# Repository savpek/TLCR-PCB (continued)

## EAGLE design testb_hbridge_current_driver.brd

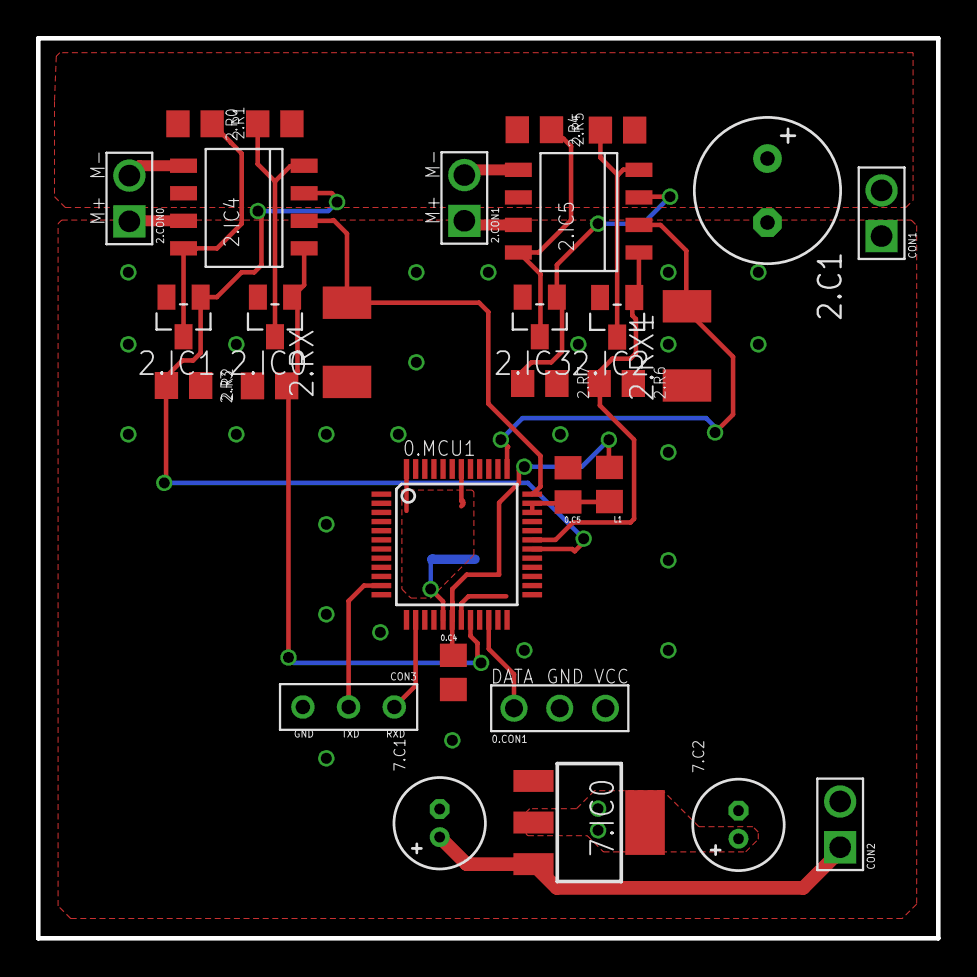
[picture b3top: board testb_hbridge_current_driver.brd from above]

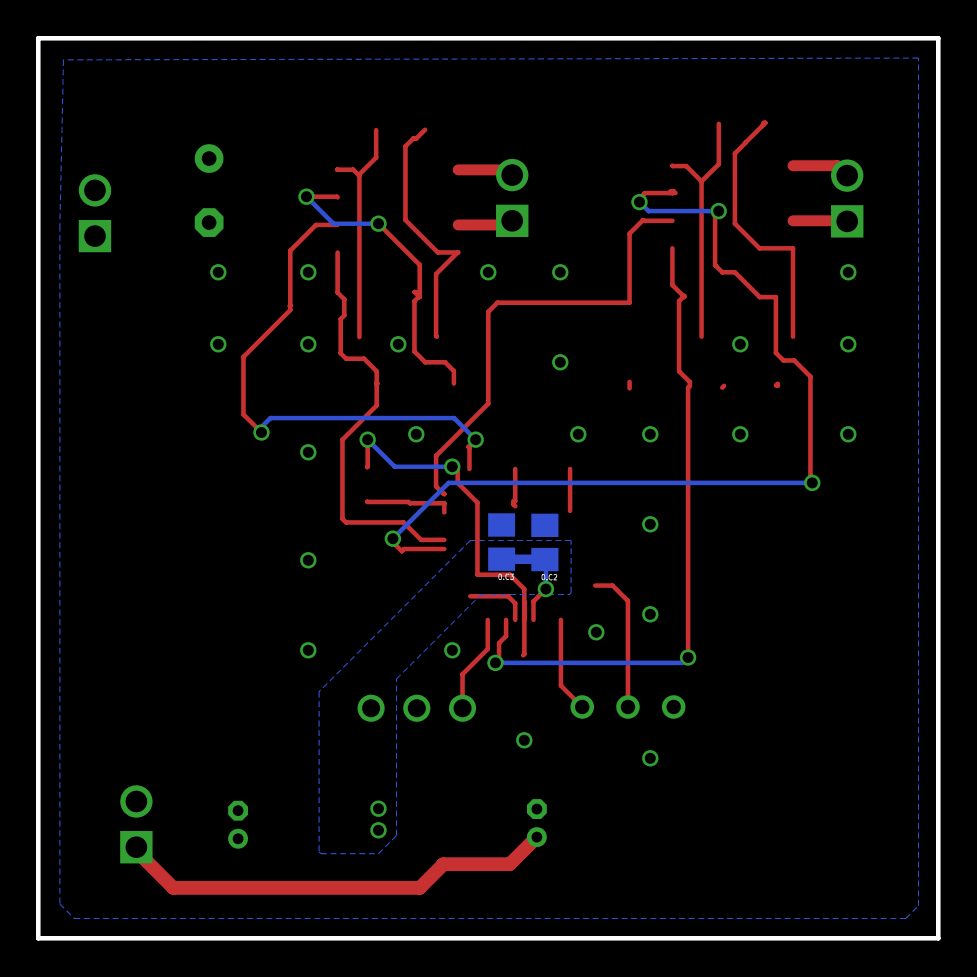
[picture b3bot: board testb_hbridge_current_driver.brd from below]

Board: 2 copper layers, 50.0 x 50.0 mm, 32 parts (2 on the bottom side), 23 nets.

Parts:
0.C2, 0.C3, 0.C4, 0.C5: 100nF; C0805
0.CON1: CONNECTOR_3PINAWIRE; 1X3_AWIRE
0.MCU1: AT32UCL016/32/64_TQFP48; TQFP48
2.C1: 220uF; E3,5-8
2.CON0, 2.CON1: CONNECTOR_2PIN1X2_MOTOR_COIL; 1X2_MOTOR_COIL_CONNECTOR
2.IC0, 2.IC1, 2.IC2, 2.IC3: N_MOSFET_TSM2N7002; SOT23
2.IC4, 2.IC5: ZXMHC6A07T8
2.R0, 2.R1, 2.R4, 2.R5: 1k; R0805
2.R2, 2.R3, 2.R6, 2.R7: 10k; R0805
2.RX, 2.RX1: 0R2; R2010
7.C1, 7.C2: 22uF; E1.5-5
7.IC0: REGULATOR_AP1117E33G-13; SOT223
CON1, CON2: CONNECTOR_2PIN1X2_WIRE; 1X2_WIRE
CON3: CONNECTOR_3PINUSART; 1X3_USART
L1: 10uH; C0805

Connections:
#RESET(AWIRE_DATA): 0.CON1.DATA, 0.MCU1.22
+3V3: 0.C2.1, 0.C3.1, 0.CON1.VCC, 0.MCU1.17, 0.MCU1.42, 0.MCU1.48, 7.C2.+, 7.IC0.2, 7.IC0.4
+12V: 2.C1.+, 2.IC4.6, 2.IC5.6, 2.R0.2, 2.R1.2, 2.R4.2, 2.R5.2, CON1.2
GND: 0.C2.2, 0.C3.2, 0.C4.2, 0.C5.2, 0.CON1.GND, 0.MCU1.1, 0.MCU1.19, 0.MCU1.33, 0.MCU1.43, 0.MCU1.45, 2.C1.-, 2.IC0.2, 2.IC1.2, 2.IC2.2, 2.IC3.2, 2.R2.1, 2.R3.1, 2.R6.1, 2.R7.1, 2.RX.1, 2.RX1.1, 7.C1.-, 7.C2.-, 7.IC0.1, CON1.1, CON2.2, CON3.GND
unnamed: 7.C1.+, 7.IC0.3, CON2.1
unnamed: 2.IC0.3, 2.IC4.4, 2.R0.1
unnamed: 2.CON0.M+, 2.IC4.7
unnamed: 2.CON0.M-, 2.IC4.5
unnamed: 0.C5.1, 0.MCU1.34, 0.MCU1.35, L1.1
unnamed: 0.C4.1, 0.MCU1.18, L1.2
unnamed: 2.IC2.3, 2.IC5.4, 2.R4.1
unnamed: 2.IC1.3, 2.IC4.8, 2.R1.1
unnamed: 2.IC3.3, 2.IC5.8, 2.R5.1
unnamed: 2.CON1.M+, 2.IC5.7
unnamed: 2.CON1.M-, 2.IC5.5
PA00(TXD0): 0.MCU1.11, CON3.TXD
PA01(RXD0): 0.MCU1.14, CON3.RXD
PA14: 0.MCU1.36, 2.IC4.2, 2.RX.2
PA15: 0.MCU1.37, 2.IC5.2, 2.RX1.2
PB05: 0.MCU1.20, 2.IC0.1, 2.IC4.1, 2.R3.2
PB06: 0.MCU1.30, 2.IC1.1, 2.IC4.3, 2.R2.2
PB07: 0.MCU1.31, 2.IC2.1, 2.IC5.1, 2.R6.2
PB8: 2.IC3.1, 2.IC5.3, 2.R7.2

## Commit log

2011-10-04 This is initial empty version of Time Lapse Camera Rail PCB.
    This is PCB version which is supposed to manufacture.
2011-10-05 Added parts to library.
    Parts added: AT32UCL, USB-B, DATAFLASH and Power Connector.
    Fixed parts also slightly during process. By fixing means
    putted FARNELL and DATASHEET attributes for each part and
    so on.
2011-10-05 Added LCD display and 3v3 regulator to library.
2011-10-06 Added encoder PEC11-4XX... and P channel mosfet NX2301P.
2011-10-06 Added FTR232RL to library.
2011-10-06 Added N channel mosfet. Fixed variant names begin with '_' mark.
2011-10-23 Ready for routing.
    Added parts necessary, all connections should be schecked to be correct.
    Board encoders, connectors and display have been arranged corresponding
    for mechanical design of TLCR (imported from DWG).
    Parts are placed to board. There may be changes however during routing
    process.
2011-10-24 Removed holes from LCD display.
    Screw holes are not needed since display will be taped on to surface.
2011-10-24 MCU unrouted.
    Routed rest of the board exept mcu and its most near peripheals.
2011-10-24 Removed one bybass condensator from MCU.
    This because 100nF condensators moved under MCU,
    Which means they all are very close of MCU power pins.
2011-10-25 Modified incorrect layerdefs of parts.
    Also shortened silkscreen of USB, JACK and POWER connectors because they go
    over dimension line.
2011-10-25 Board routed.
    Everything should be connected, and DRC check passed (notice width ignores).
    Now only thing left is to fix silkscreen.
2011-10-25 First version of silkscreen is ready.
    Connectors silkscreen may still require tweaking.
2011-10-26 Fixed silkscreen and moved 12.R2 away from 12.L1 coil.
    15uH coil and 12.R2 resistor were too close of each other.
    Fixed values places so that device is easier to assembly later.
    Fixed few text sizes from t.names.
    Redrawed 15uH inductor silkscreen footage (now corresponding true size of device).
    Checked few more of pads (inductor and 1k trimmer).
2011-12-26 Changed silksreen text size to 30mil as requested from PCB cart.
    Seems PCB cart cannot quarantee better resolution for texts.
2012-02-03 Fixed errornous connection from 3V3 to VDDCORE.
    This pin should float in this configuration since device
    has internal 1.8V regulator for internal logig.
2012-02-05 Made test version of new H-Bridge driver.
    Board is named: testb_hbridge_driver.
    Manufactured at iTeadStudios.
    Board includes current measurement and 2x of new H-Bridges. If HW
    works need to write driver which supports accurate microstepping.
2012-03-01 Rebuilded directory structure for project.
    Now subfolders include testboards etc... They are under their own
    git however.
2012-03-01 Moved tesboard off from main project.
2012-07-19 Moved testboards to subproject.
2012-07-27 Removed backup files.
2012-07-27 Added readme.
2014-03-09 Schematic seems to be ready.
2014-03-23 PCB layout ready.
